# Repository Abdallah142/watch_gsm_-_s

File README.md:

# SmartCare Diabetes

## Overview
This project is a smart bracelet that monitors heart rate, oxygen saturation, temperature, and sends this data via SMS to caregivers using an ESP32 microcontroller, MAX30102 sensor, DS18B20 temperature sensor, and an OLED display. When caregivers respond via SMS, the data is displayed on the OLED screen.

---

## Components Required
- **ESP32 Development Board**
- **MAX30102 Pulse Oximeter and Heart Rate Sensor**
- **DS18B20 Temperature Sensor**
- **OLED Display (e.g., 128x64 I2C OLED)**
- **GSM Module (e.g., SIM800L, SIM900)**
- **2 x 26650 Li-Ion Rechargeable Batteries (3.7V, 3000mAh each, Total: 6000mAh)**
- **Battery Management System (BMS)**
- **Jumper wires and Breadboard**
- **Resistors (for DS18B20 and MAX30102 connections)**

---

## Libraries Required
You will need to install the following libraries for your project:

1. **Adafruit MAX30105** (For MAX30102 sensor)
   - Install: `Sketch > Include Library > Manage Libraries`, search for "Adafruit MAX30105" and install it.

2. **OneWire** (For DS18B20 sensor)
   - Install: `Sketch > Include Library > Manage Libraries`, search for "OneWire" and install it.

3. **DallasTemperature** (For DS18B20 sensor)
   - Install: `Sketch > Include Library > Manage Libraries`, search for "DallasTemperature" and install it.

4. **Adafruit SSD1306** (For OLED Display)
   - Install: `Sketch > Include Library > Manage Libraries`, search for "Adafruit SSD1306" and install it.

5. **SoftwareSerial** (For GSM module communication, if not already available)
   - This is typically included by default in Arduino IDE.

6. **TinyGsmClient** (For GSM communication)
   - Install: `Sketch > Include Library > Manage Libraries`, search for "TinyGsmClient" and install it.

---

## Setting Up ESP32 in Arduino IDE

To use the ESP32 in Arduino IDE, follow these steps:

1. **Install the ESP32 Board Manager URL:**
   - Open Arduino IDE.
   - Go to `File > Preferences`.
   - In the "Additional Boards Manager URLs" field, add the following URL:
     ```
     https://dl.espressif.com/dl/package_esp32_index.json
     ```

2. **Install ESP32 Board:**
   - Go to `Tools > Board > Boards Manager`.
   - Search for `esp32` and click "Install" to add the ESP32 boards to your IDE.

3. **Select the Correct Board and Port:**
   - Go to `Tools > Board` and select `ESP32 Dev Module` (or your specific ESP32 model).
   - Go to `Tools > Port` and select the appropriate COM port for your ESP32.

---

## Wiring Diagram

Here is the wiring configuration for the components:

#### MAX30102 (Pulse Oximeter and Heart Rate Sensor)
| MAX30102 Pin     | ESP32 Pin  |
|------------------|------------|
| VCC              | 3.3V       |
| GND              | GND        |
| SDA              | GPIO 21    |
| SCL              | GPIO 22    |

#### DS18B20 (Temperature Sensor)
| DS18B20 Pin      | ESP32 Pin  |
|------------------|------------|
| VCC              | 3.3V       |
| GND              | GND        |
| Data             | GPIO 17    |
| Resistor (4.7kΩ) | Between Data and VCC |

#### OLED Display (128x64 I2C)
| OLED Pin         | ESP32 Pin  |
|------------------|------------|
| VCC              | 3.3V       |
| GND              | GND        |
| SDA              | GPIO 21    |
| SCL              | GPIO 22    |

#### GSM Module (e.g., SIM800L)
| GSM Pin          | ESP32 Pin  |
|------------------|------------|
| VCC              | 5V         |
| GND              | GND        |
| TX               | GPIO 16    |
| RX               | GPIO 17    |

#### Battery and BMS
| BMS Pin          | ESP32 Pin  |
|------------------|------------|
| VCC              | 5V         |
| GND              | GND        |

---

## Power Consumption
To estimate the runtime of the project with a combined 6000mAh battery capacity, we calculated the total current draw of all components.

### Current Draw of Components
- **ESP32**: ~80mA (average)
- **GSM Module**: ~200mA (average, can spike up to 2A during transmission)
- **MAX30102**: ~10mA (average)
- **DS18B20**: ~1mA (average)
- **OLED Display**: ~20mA (average)

### Total Average Current
\[ \text{Total average current} = 80mA (ESP32) + 200mA (GSM) + 10mA (MAX30102) + 1mA (DS18B20) + 20mA (OLED) = 311mA \]

### Combined Battery Capacity
\[ \text{Battery capacity} = 6000mAh \]

### Estimated Runtime
To find the runtime:
\[ \text{Runtime (hours)} = \frac{\text{Battery capacity (mAh)}}{\text{Total average current (mA)}} \]
\[ \text{Runtime} = \frac{6000mAh}{311mA} \approx 19.29 \text{ hours} \]

With a combined battery capacity of 6000mAh and an average current draw of 311mA, the project is estimated to run for approximately 19.29 hours. This is a theoretical estimate, and actual runtime may vary based on real-world factors such as peak current draws, battery health, and efficiency of the power management in the circuit.

---

## Power Management

1. **Battery Considerations:**
   - The **26650 Li-Ion** batteries with a **BMS** are responsible for powering the ESP32 and sensors.
   - Ensure the **BMS** is properly managing the charging and discharging of the batteries to prevent damage.
   - Consider adding a low battery detection system to avoid power loss.

---

## Conclusion

This project combines the ESP32's capabilities with multiple sensors to create a smart bracelet that monitors vital signs and sends updates to caregivers via SMS. The data is displayed on the OLED screen in real-time, ensuring that caregivers can always stay informed.

---

## License

This project is licensed under the MIT License.

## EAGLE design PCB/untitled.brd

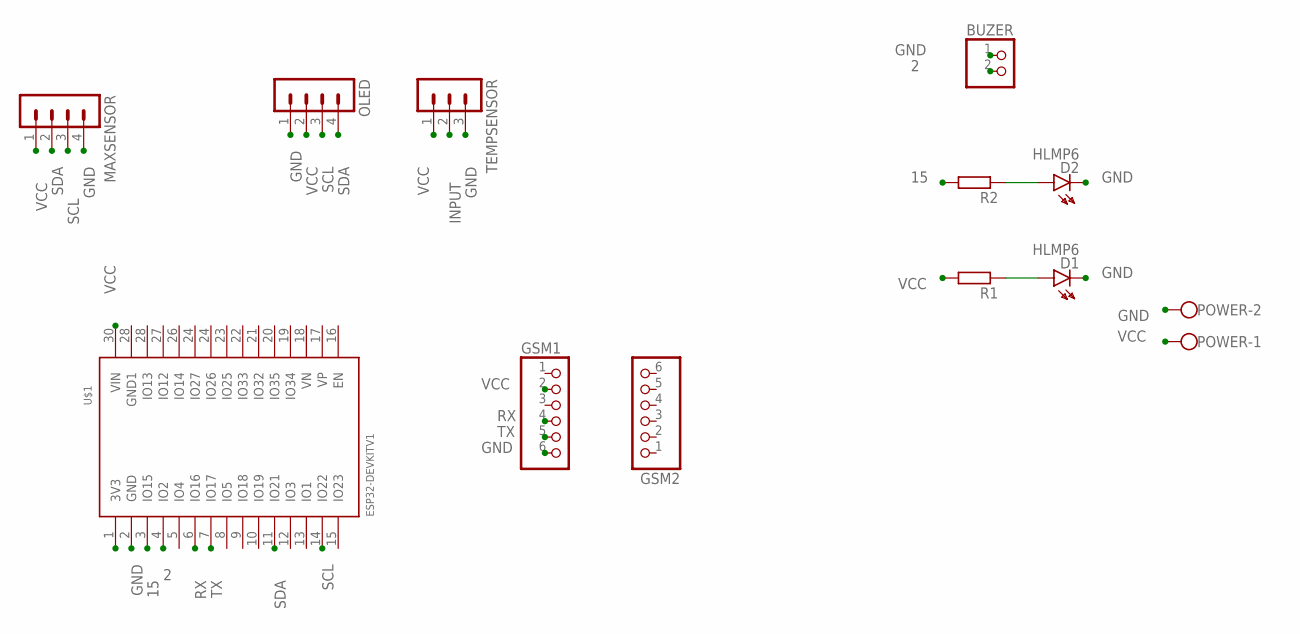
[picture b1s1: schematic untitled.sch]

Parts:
BUZER: PINHD-1X2; 1X02
D1, D2: HLMP6
GSM1, GSM2: PINHD-1X6; 1X06
MAXSENSOR: MA04-1
OLED: MA04-1
POWER: W237-102
R1, R2: R-EU_0204/5; 0204/5
TEMPSENSOR: MA03-1
U$1: ESP32DEVKITV1; ESP32-DEVKITV1

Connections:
2: BUZER.2, U$1.4 (IO2)
15: R2.2, U$1.3 (IO15)
GND: BUZER.1, D1.K, D2.K, GSM1.6, MAXSENSOR.4, OLED.1, POWER.2, TEMPSENSOR.3, U$1.2 (GND)
INPUT: TEMPSENSOR.2
unnamed: D2.A, R2.1
unnamed: D1.A, R1.1
RX: GSM1.4, U$1.6 (IO16)
SCL: MAXSENSOR.3, OLED.3, U$1.14 (IO22)
SDA: MAXSENSOR.2, OLED.4, U$1.11 (IO21)
TX: GSM1.5, U$1.7 (IO17)
VCC: GSM1.2, MAXSENSOR.1, OLED.2, POWER.1, R1.2, TEMPSENSOR.1, U$1.30 (VIN)

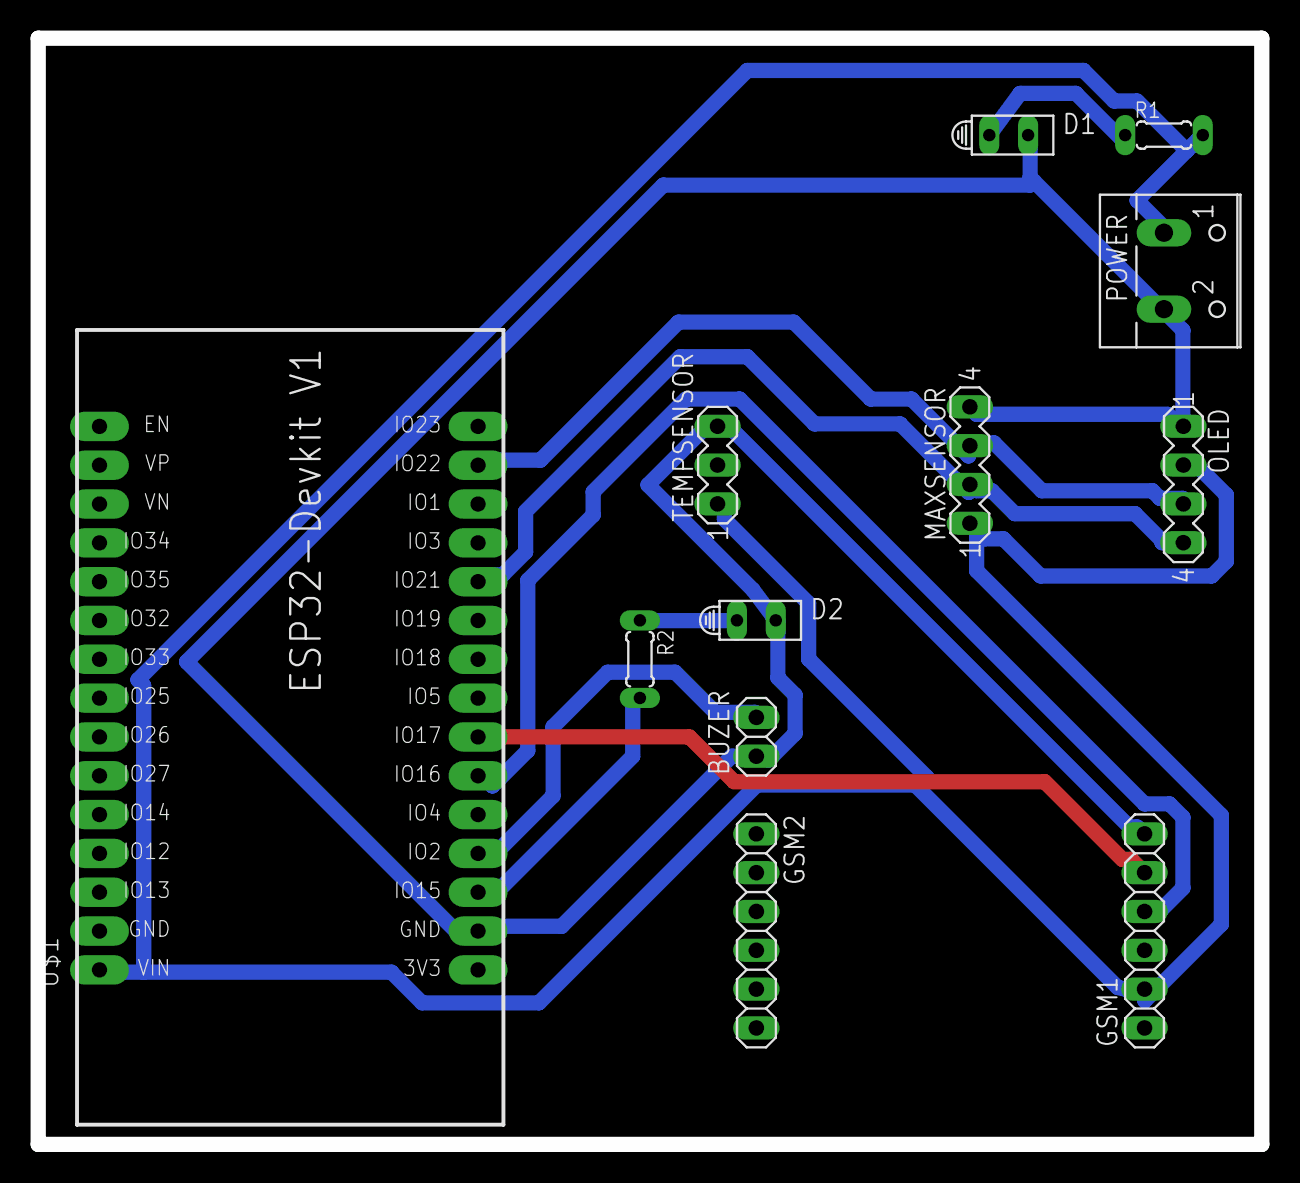
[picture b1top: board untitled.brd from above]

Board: 2 copper layers, 80.1 x 72.4 mm, 12 parts (0 on the bottom side), 10 nets.

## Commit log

2024-11-09 test
2024-11-09 test of oled
2024-11-15 test oled and max sensor
2024-11-15 test_gsm_oled_max
2024-11-16 photo
2024-11-16 photo of com
2024-12-02 Update test
